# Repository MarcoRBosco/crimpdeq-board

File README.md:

# Crimpdeq board

TODO

## Where to buy

TODO

## Project Specification

TODO

### Futures

### I2C Peripherals

This board includes the following peripherals over the I2C bus:

| Peripheral               | Part number | Reference                                                                                                      | Crate                                     | Address |
| ------------------------ | ----------- | -------------------------------------------------------------------------------------------------------------- | ----------------------------------------- | ------- |
| IMU                      | ICM-42670-P | [Datasheet](https://invensense.tdk.com/download-pdf/icm-42670-p-datasheet/)                                    | [Link](https://crates.io/crates/icm42670) | 0x68    |
| Temperature and Humidity | SHTC3       | [Datasheet](https://www.mouser.com/datasheet/2/682/Sensirion_04202018_HT_DS_SHTC3_Preliminiary_D2-1323493.pdf) | [Link](https://crates.io/crates/shtcx)    | 0x70    |

TODO: Add Maxim gauge and cell load ADCs

#### I2C Bus Connection

| Signal | GPIO   |
| ------ | ------ |
| SDA    | GPIO10 |
| SCL    | GPIO8  |

TODO: Add Maxim gauge and cell load ADCs

### I/Os

The following devices are connected through GPIO:

| I/O Devices | GPIO  |
| ----------- | ----- |
| WS2812 LED  | GPIO2 |
| LED         | GPIO7 |
| Button/Boot | GPIO9 |

TODO: Add battery leds

### Power

* USB type-C (*no PD compatibility*).
* Li-Ion battery charger - MCP73831T-2ACI/OT, it charges up to 4.2V.
  * Recommendation: MCP73831T-2ACI/OT does not provide battery protection for over-current or over-discharge. For the battery (Li-Ion or Li-Po), it's recommended the ones with embedded protection
  * Limitation: reading the battery voltage is not supported.

### Pin Layout

TODO

## Project KiCad Libraries

* [Espressif KiCad Libraries v3.0.2](https://github.com/espressif/kicad-libraries/releases/tag/3.0.2)
* [UAMP KiCad Libraries v1.0.1](https://github.com/uampio/UAMP-KiCad-Libraries/releases/tag/1.0.1)

## Board Design

Top

TODO

Bottom

TODO

## Bill of Material

TODO

## Case

TODO

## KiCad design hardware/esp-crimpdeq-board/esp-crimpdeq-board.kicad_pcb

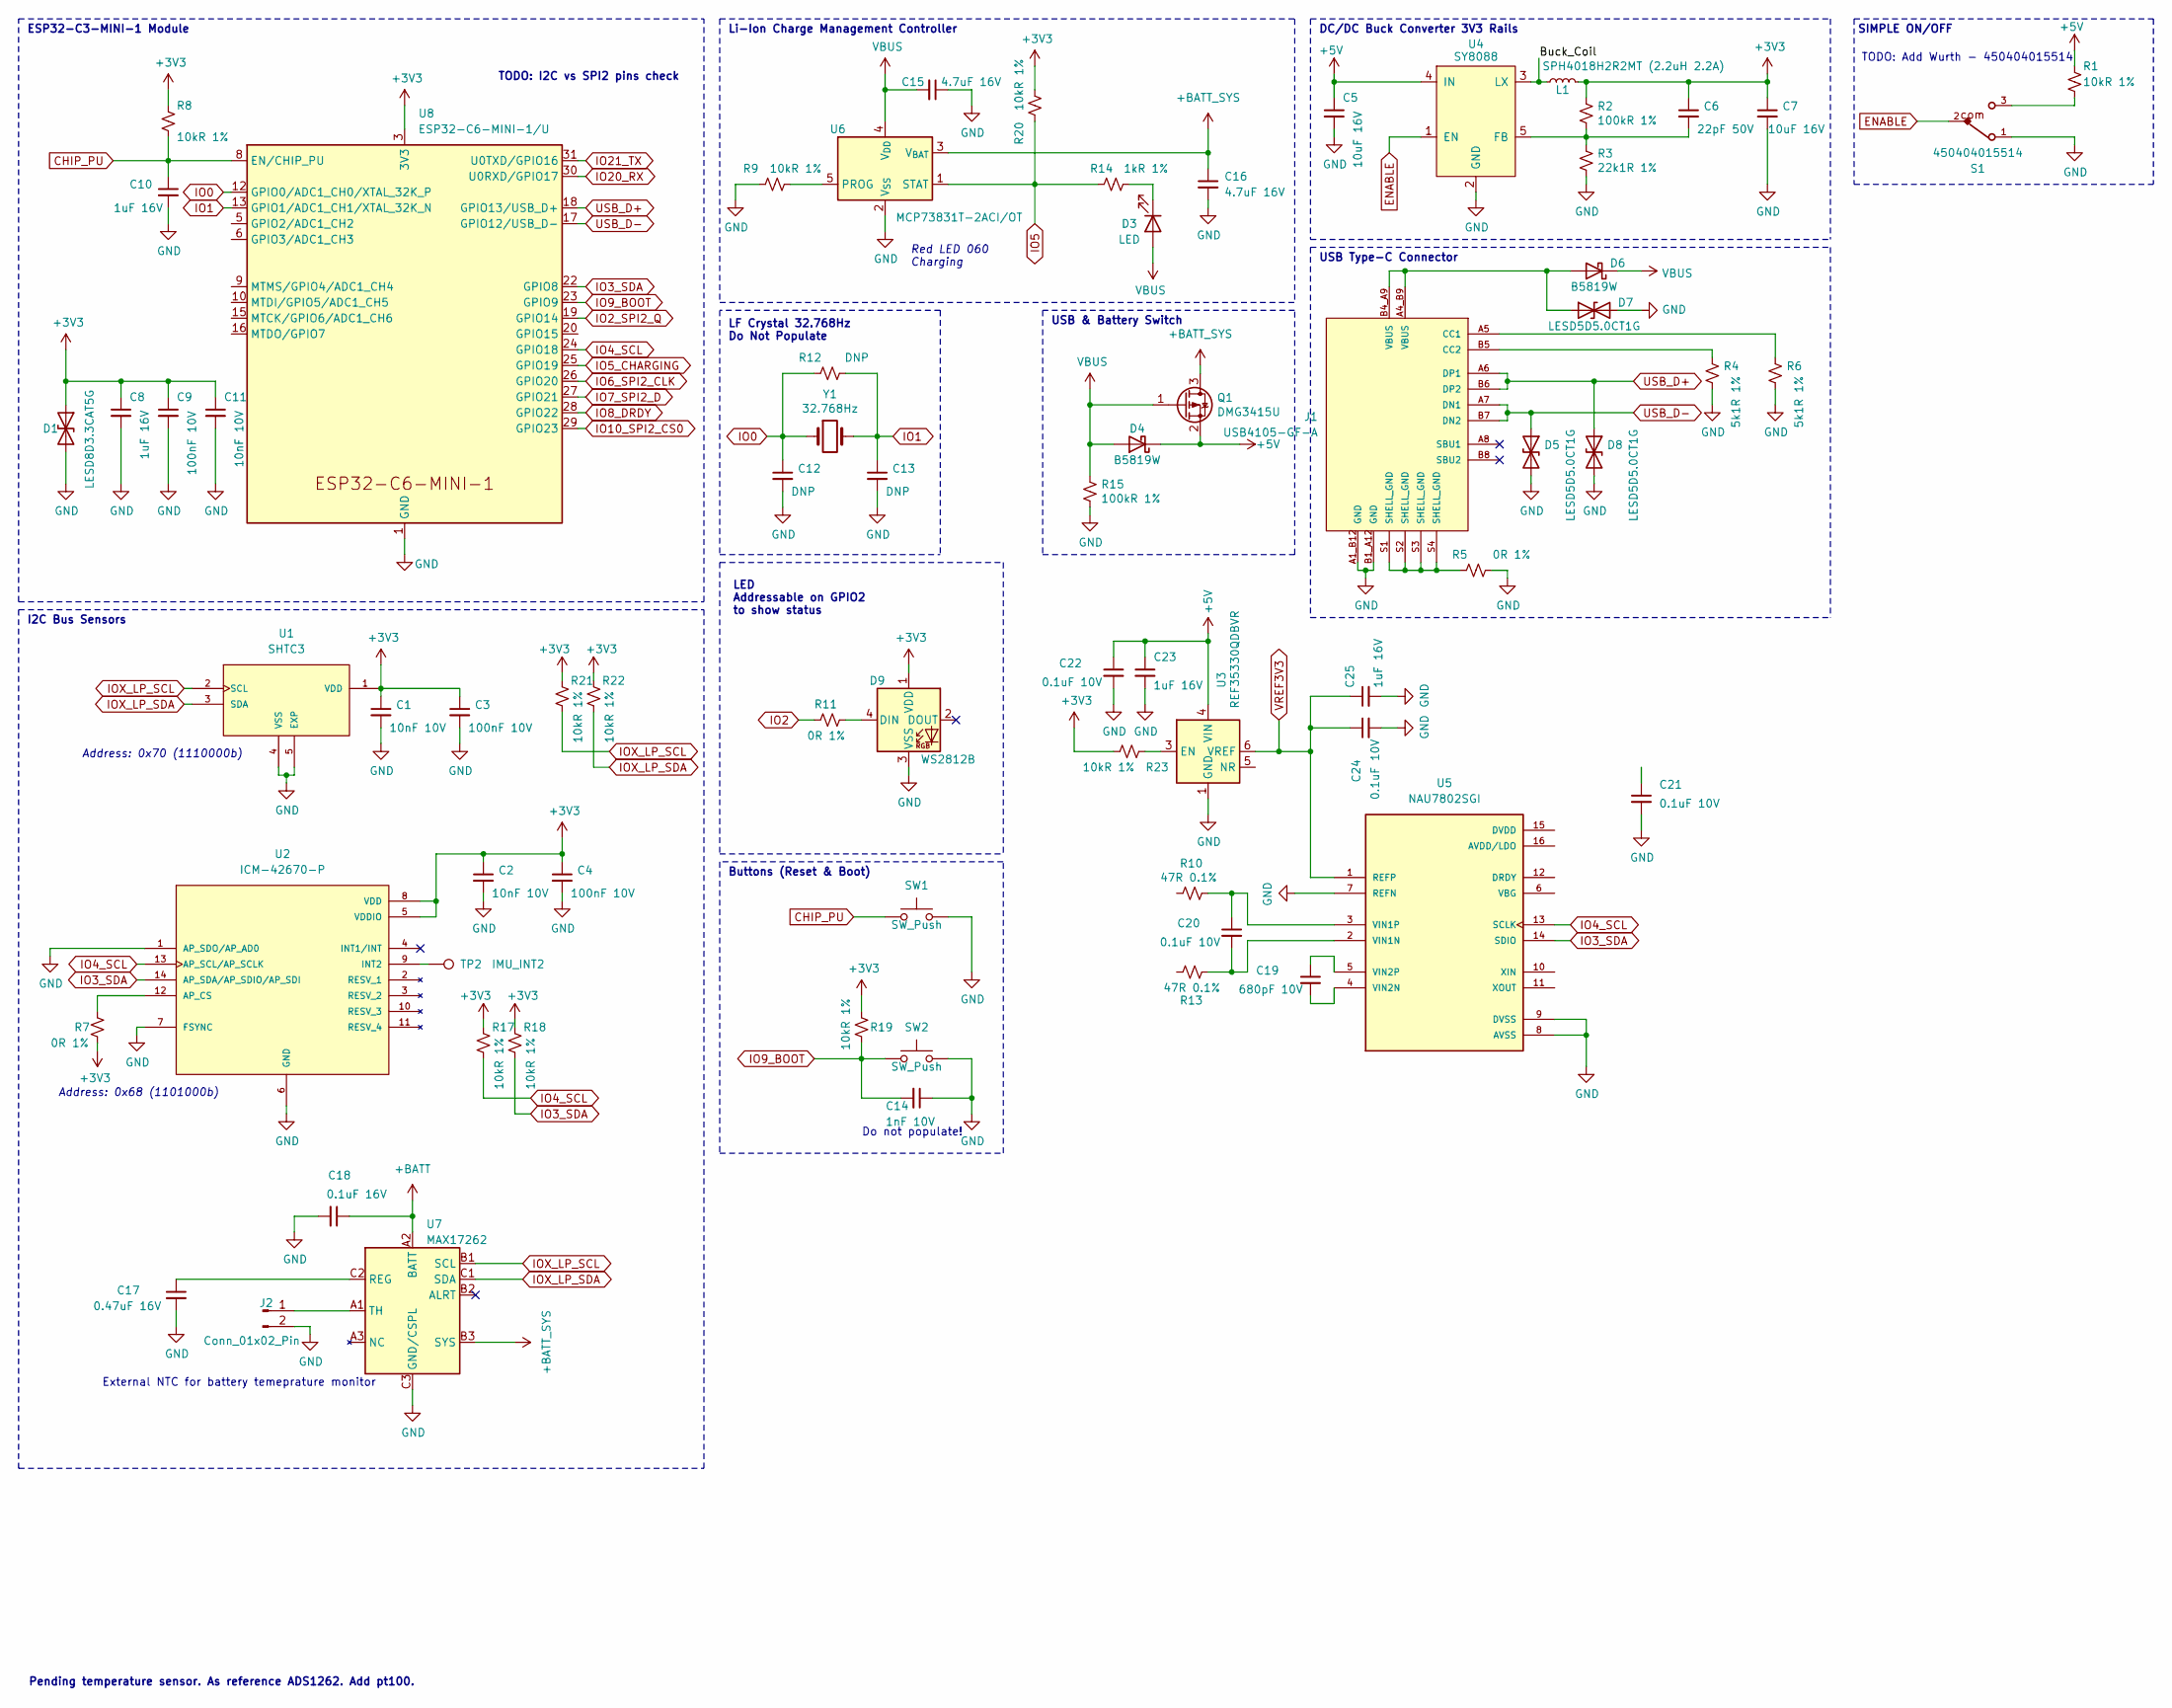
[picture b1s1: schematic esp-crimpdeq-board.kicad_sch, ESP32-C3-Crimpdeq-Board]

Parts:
C1, C2, C11: 10nF 10V; C_0402_1005Metric; LCSC C15195
C3, C4, C9: 100nF 10V; C_0402_1005Metric; LCSC C1525
C5, C7: 10uF 16V; C_0805_2012Metric; LCSC C15850
C6: 22pF 50V; C_0603_1608Metric; LCSC C1653
C8, C10, C23, C25: 1uF 16V; C_0402_1005Metric; LCSC C52923
C12, C13: DNP; C_0402_1005Metric
C14: 1nF 10V; C_0402_1005Metric; LCSC C1523
C15, C16: 4.7uF 16V; C_0603_1608Metric; LCSC C19666
C17: 0.47uF 16V; C_0603_1608Metric; LCSC C19666
C18: 0.1uF 16V; C_0603_1608Metric; LCSC C19666
C19: 680pF 10V; C_0402_1005Metric; LCSC C15195
C20, C21, C22, C24: 0.1uF 10V; C_0402_1005Metric; LCSC C15195
D1: LESD8D3.3CAT5G; SOD-882; LCSC C172409
D3: LED; LED_0603_1608Metric; LCSC C2286
D4, D6: B5819W; D_SOD-123; LCSC C8598
D5, D7, D8: LESD5D5.0CT1G; D_SOD-523; LCSC C383211
D9: WS2812B; LED_WS2812B_PLCC4_5.0x5.0mm_P3.2mm; LCSC C527089
J1: USB4105-GF-A; GCT_USB4105-GF-A; PARTREV A3
J2: Conn_01x02_Pin
L1: SPH4018H2R2MT (2.2uH 2.2A); L_Bourns-SRN4018; LCSC C370436
Q1: DMG3415U; SOT-23; LCSC C96616
R1, R8, R9, R17, R18, R19, R20, R21, R22, R23: 10kR 1%; R_0402_1005Metric; LCSC C25744
R2, R15: 100kR 1%; R_0402_1005Metric; LCSC C25741
R3: 22k1R 1%; R_0402_1005Metric; LCSC C43473
R4, R6: 5k1R 1%; R_0402_1005Metric; LCSC C25905
R5, R7, R11: 0R 1%; R_0402_1005Metric; LCSC C17168
R10, R13: 47R 0.1%; R_0402_1005Metric; LCSC C25905
R12: DNP; R_0402_1005Metric
R14: 1kR 1%; R_0402_1005Metric; LCSC C11702
S1: 450404015514
SW1, SW2: SW_Push; SW_SPST_PTS810; LCSC C116501
TP2: IMU_INT2; TestPoint_Pad_D1.0mm
U1: SHTC3; SON100P200X200X80-5N; PARTREV 3
U2: ICM-42670-P; IC_ICM-42670-P; PARTREV 1.0
U3: REF35330QDBVR; SOT-23-6
U4: SY8088; SOT-23-5
U5: NAU7802SGI; SOP-16_3.9x9.9mm_P1.27mm; PARTREV 2.6
U6: MCP73831T-2ACI/OT; SOT-23-5; LCSC C424093
U7: MAX17262; WLP-9_1.468x1.448mm_Layout3x3_P0.4mm
U8: ESP32-C6-MINI-1/U; ESP32-C6-MINI-1
Y1: 32.768Hz; Crystal_SMD_3215-2Pin_3.2x1.5mm

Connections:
+3V3: C1.1, C2.1, C3.1, C4.1, C6.1, C7.1, C8.1, C9.1, C11.1, D1.1 (A1), D9.1 (VDD), L1.2, R2.1, R7.2, R8.1, R17.1, R18.1, R19.1, R20.2, R21.1, R22.1, R23.2, U1.1 (VDD), U2.5 (VDDIO), U2.8 (VDD), U8.3 (3V3)
+5V: C5.1, C22.1, C23.1, D4.1 (K), Q1.2 (S), R1.1, U3.4 (VIN), U4.4 (IN)
+BATT: C18.1, U7.A2 (BATT)
+BATT_SYS: C16.1, Q1.3 (D), U6.3 (V_{BAT}), U7.B3 (SYS)
/Buck_Coil: L1.1, U4.3 (LX)
CHIP_PU: C10.1, R8.2, SW1.1, U8.8 (EN/CHIP_PU)
ENABLE: S1.2, U4.1 (EN)
IO0: C12.1, R12.1, U8.12 (GPIO0/ADC1_CH0/XTAL_32K_P), Y1.1
IO1: C13.1, R12.2, U8.13 (GPIO1/ADC1_CH1/XTAL_32K_N), Y1.2
IO2: R11.1
IO2_SPI2_Q: U8.19 (GPIO14)
IO3_SDA: R18.2, U2.14 (AP_SDA/AP_SDIO/AP_SDI), U5.14 (SDIO), U8.22 (GPIO8)
IO4_SCL: R17.2, U2.13 (AP_SCL/AP_SCLK), U5.13 (SCLK), U8.24 (GPIO18)
IO5: R14.1, R20.1, U6.1 (STAT)
IO5_CHARGING: U8.25 (GPIO19)
IO6_SPI2_CLK: U8.26 (GPIO20)
IO7_SPI2_D: U8.27 (GPIO21)
IO8_DRDY: U8.28 (GPIO22)
IO9_BOOT: C14.2, R19.2, SW2.1, U8.23 (GPIO9)
IO10_SPI2_CS0: U8.29 (GPIO23)
IO20_RX: U8.30 (U0RXD/GPIO17)
IO21_TX: U8.31 (U0TXD/GPIO16)
IOX_LP_SCL: R21.2, U1.2 (SCL), U7.B1 (SCL)
IOX_LP_SDA: R22.2, U1.3 (SDA), U7.C1 (SDA)
unnamed: D3.1 (K), R14.2
unnamed: D6.2 (A), D7.1 (A1), J1.A4_B9 (VBUS), J1.B4_A9 (VBUS)
unnamed: D9.4 (DIN), R11.2
unnamed: J1.A5 (CC1), R6.1
unnamed: J1.B5 (CC2), R4.1
unnamed: J1.S1 (SHELL_GND), J1.S2 (SHELL_GND), J1.S3 (SHELL_GND), J1.S4 (SHELL_GND), R5.1
unnamed: J2.1, U7.A1 (TH)
unnamed: R1.2, S1.3
unnamed: R23.1, U3.3 (EN)
unnamed: R7.1, U2.12 (AP_CS)
unnamed: TP2.1, U2.9 (INT2)
unnamed: C24.1, C25.1, U3.6 (VREF), U5.1 (REFP)
unnamed: C6.2, R2.2, R3.1, U4.5 (FB)
unnamed: C20.2, R13.2, U5.2 (VIN1N)
unnamed: C20.1, R10.2, U5.3 (VIN1P)
unnamed: C19.2, U5.4 (VIN2N)
unnamed: C19.1, U5.5 (VIN2P)
unnamed: R9.2, U6.5 (PROG)
unnamed: C17.1, U7.C2 (REG)
USB_D+: D8.1 (A1), J1.A6 (DP1), J1.B6 (DP2), U8.18 (GPIO13/USB_D+)
USB_D-: D5.1 (A1), J1.A7 (DN1), J1.B7 (DN2), U8.17 (GPIO12/USB_D-)
VBUS: C15.2, D3.2 (A), D4.2 (A), D6.1 (K), Q1.1 (G), R15.1, U6.4 (V_{DD})

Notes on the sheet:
USB Type-C Connector
Do not populate!
Buttons (Reset & Boot)
Address: 0x70 (1110000b)
Red LED 060 Charging
LF Crystal 32.768Hz Do Not Populate
TODO: Add Wurth - 450404015514
DC/DC Buck Converter 3V3 Rails
USB & Battery Switch
Pending temperature sensor. As reference ADS1262. Add pt100.
TODO: I2C vs SPI2 pins check
LED Addressable on GPIO2 to show status
Address: 0x68 (1101000b)
ESP32-C3-MINI-1 Module
Li-Ion Charge Management Controller
SIMPLE ON/OFF
I2C Bus Sensors
External NTC for battery temeprature monitor

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
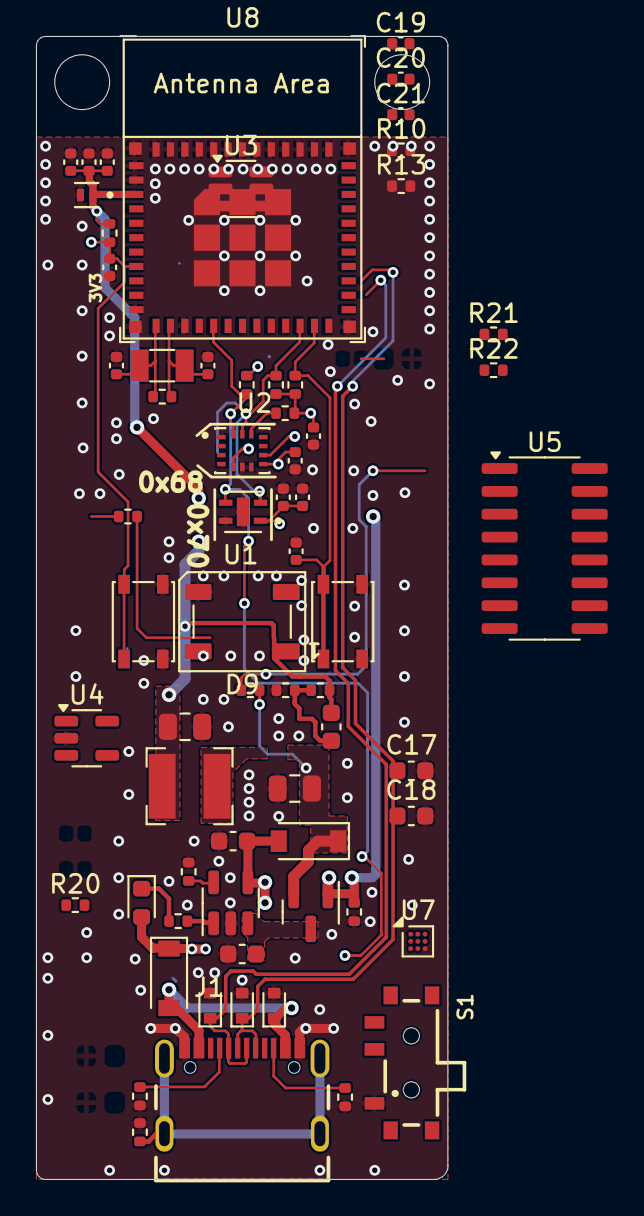
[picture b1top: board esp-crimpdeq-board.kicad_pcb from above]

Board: 2 copper layers, 22.9 x 63.5 mm, 66 parts (1 on the bottom side), 37 nets.

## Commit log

2025-04-30 Work still to do.
2025-05-02 Update README.md
    Updated to current state
2025-05-02 Updated espressif kicad libraries and removed some unecessary libs
2025-05-02 Added veresion
2025-05-04 Changed link libraries
2025-05-04 Added notes
2025-05-04 Added gauge
2025-05-05 ADC updated
2025-05-08 Changed micro
2025-05-08 Cahnged uC
2025-05-08 + work
2025-05-11 Updated README.md with uamp last libraries
2025-05-16 Schematic ready to review. Pending some footprints. Pending to add PN.
2025-06-24 Final schematic
    Pending footprints. Review battery connector pins.
2025-06-26 feat: Rename pins and reorganize
2025-06-26 Changed direction of clk
2025-06-26 Update esp-crimpdeq-board.kicad_sch
    Minor pinout change
2025-06-26 Separated in sheets
    -Pending expose lines.
    -Change DC/DC
    -ADS1235
2025-06-26 Added power management
2025-06-26 Pending
    Pending
2025-06-26 Added secns SY8088 to produce 5 V for fast adc
2025-06-26 Added 5V to ADC
2025-06-27 Ordering sdchematic in different sheets
2025-06-30 ci: Remove issues workflow
2025-06-30 feat: Update gitingore
2025-06-30 Remove ignored autosave and lock files
2025-06-30 feat: Organice schematic
2025-07-05 Cleaned schematic
    - Pending connectors
    - Pending BOM and footprints review
